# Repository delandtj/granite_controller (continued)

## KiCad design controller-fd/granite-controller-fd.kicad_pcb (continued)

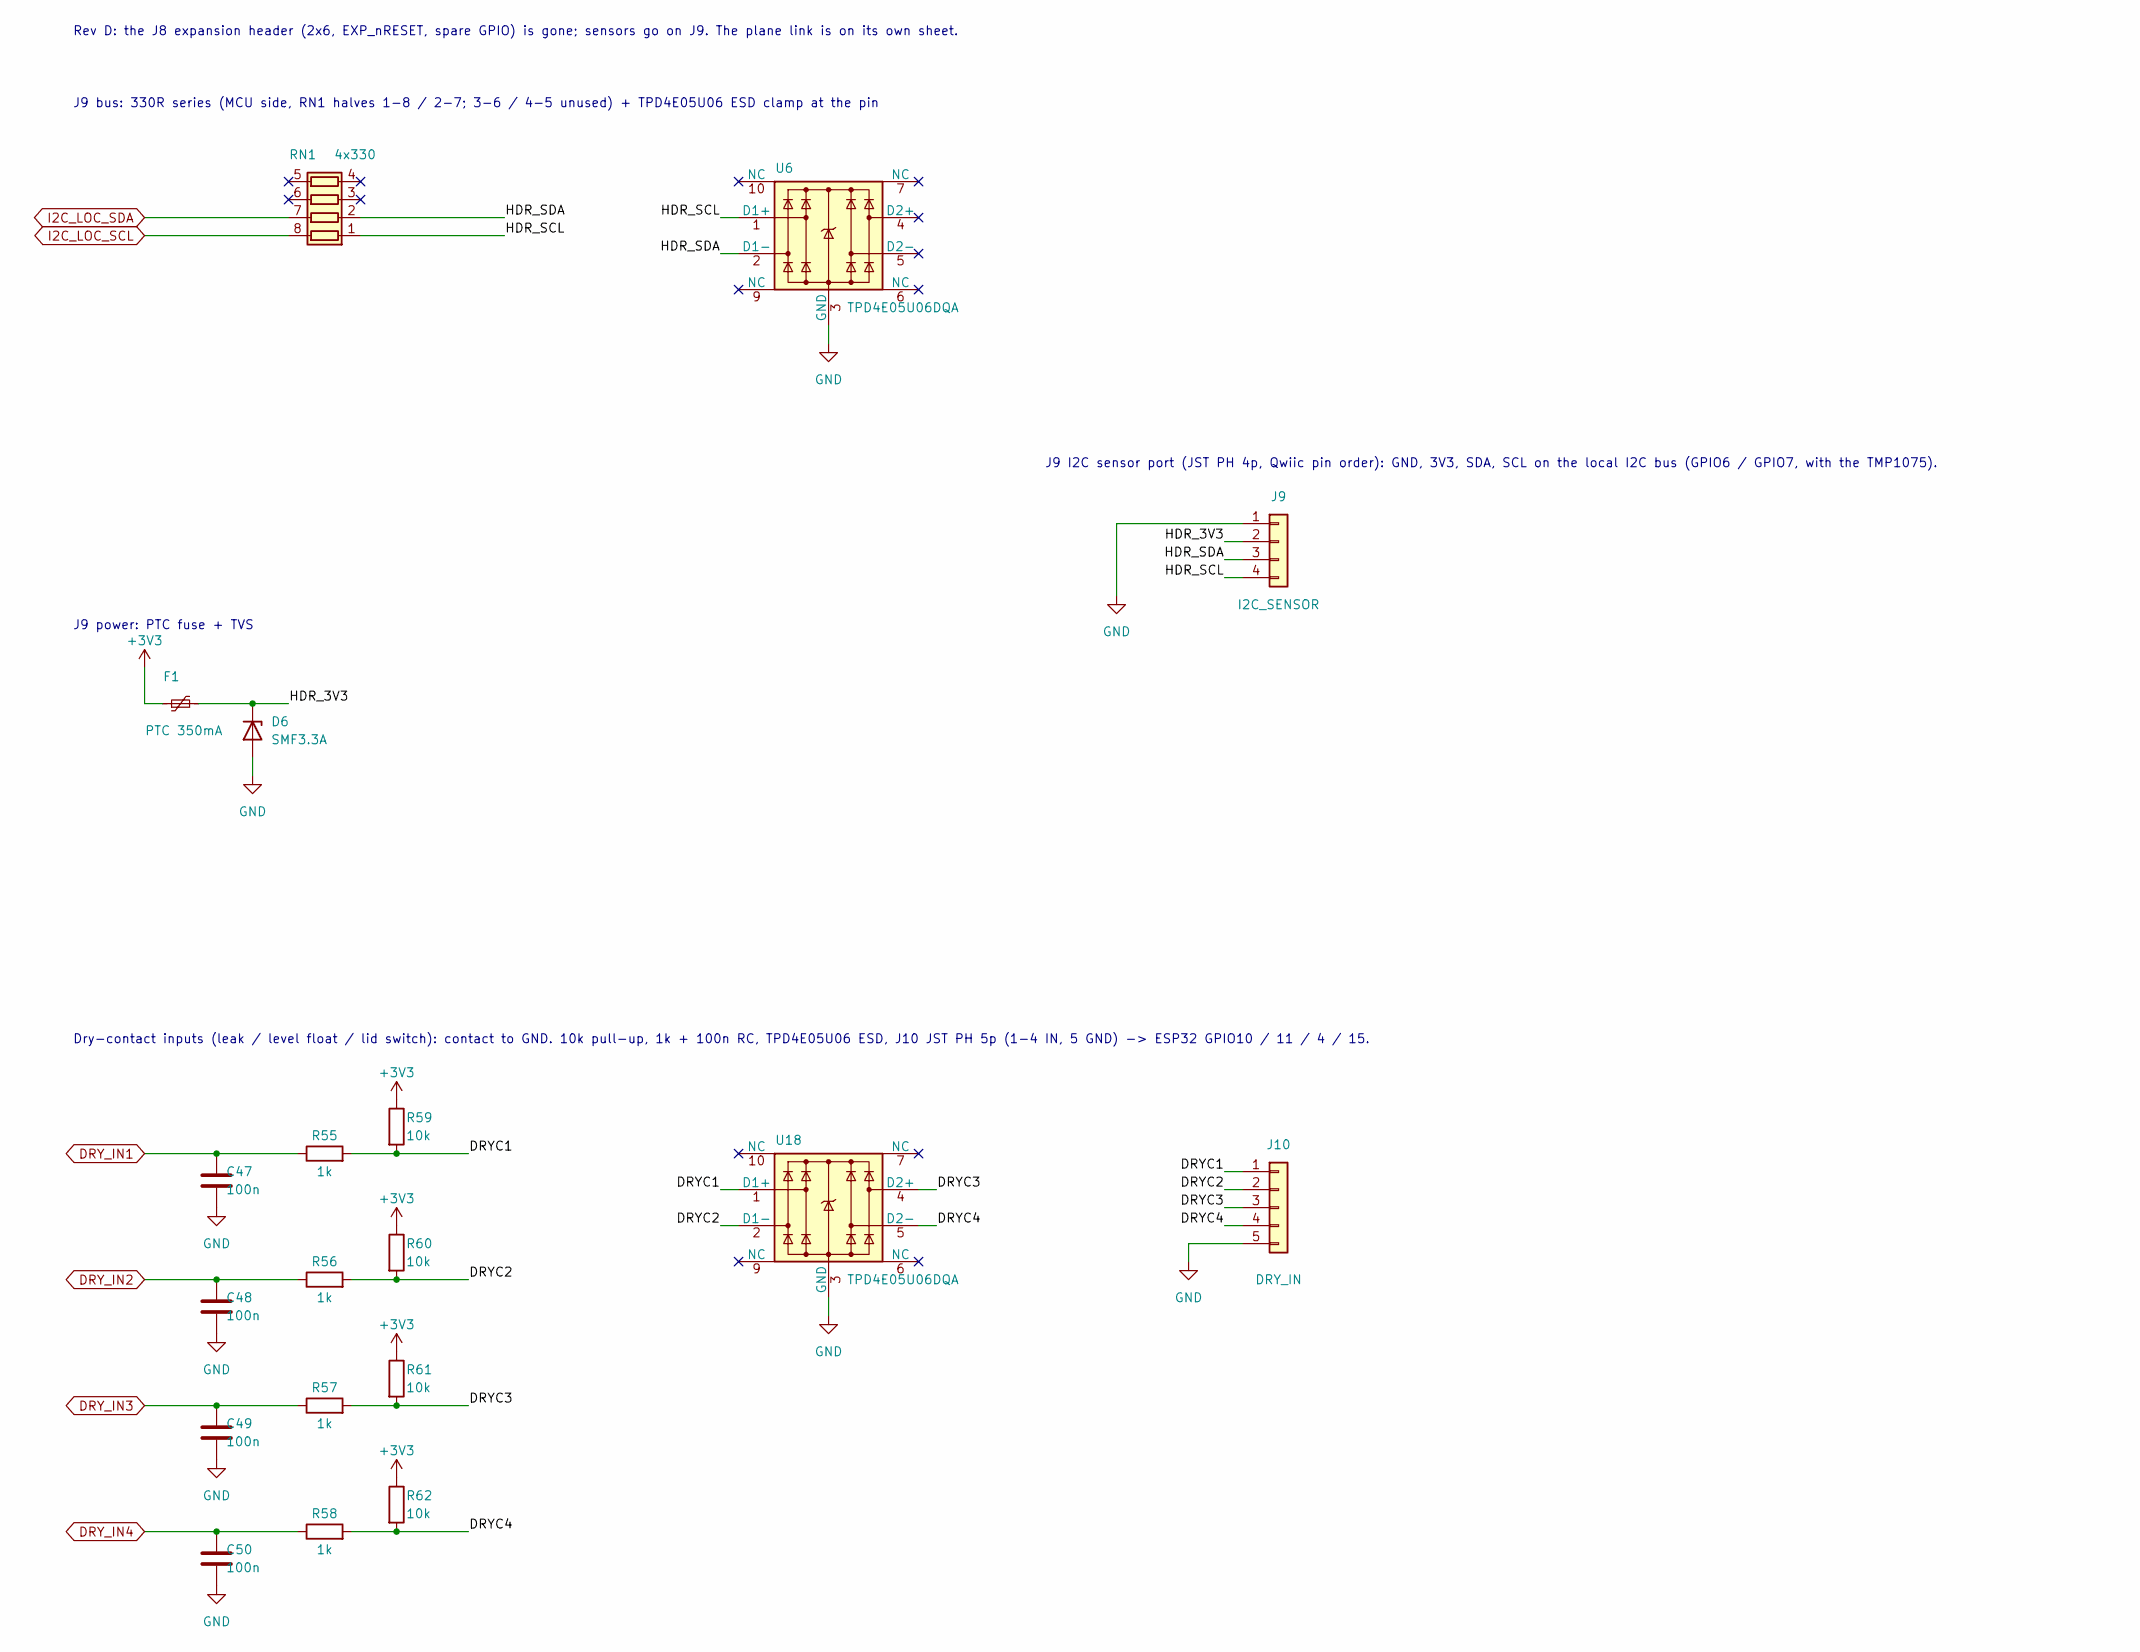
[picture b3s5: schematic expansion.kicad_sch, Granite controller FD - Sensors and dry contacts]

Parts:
C47, C48, C49, C50: 100n; C_0402_1005Metric; MPN CL05B104KO5NNNC; LCSC C1525
D6: SMF3.3A; D_SOD-123F; MPN SMF3.3A; LCSC C37331473
F1: PTC 350mA; Fuse_0805_2012Metric; MPN 0805L035/24XR; LCSC C7472565
J9: I2C_SENSOR; JST_PH_B4B-PH-K_1x04_P2.00mm_Vertical; MPN B4B-PH-K-S(LF)(SN); LCSC C131334
J10: DRY_IN; JST_PH_B5B-PH-K_1x05_P2.00mm_Vertical; MPN B5B-PH-K-S(LF)(SN); LCSC C157993
R55, R56, R57, R58: 1k; R_0402_1005Metric; MPN 0402WGF1001TCE; LCSC C11702
R59, R60, R61, R62: 10k; R_0402_1005Metric; MPN 0402WGF1002TCE; LCSC C25744
RN1: 4x330; R_Array_Convex_4x0402; MPN 4D02WGJ0331TCE; LCSC C43557
U6, U18: TPD4E05U06DQA; USON-10_2.5x1.0mm_P0.5mm; MPN TPD4E05U06DQAR; LCSC C138714

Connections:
+3V3: F1.1, R59.1, R60.1, R61.1, R62.1; also elsewhere on the board
/Sensors and dry contacts/DRYC1: J10.1, R55.2, R59.2, U18.1 (D1+)
/Sensors and dry contacts/DRYC2: J10.2, R56.2, R60.2, U18.2 (D1-)
/Sensors and dry contacts/DRYC3: J10.3, R57.2, R61.2, U18.4 (D2+)
/Sensors and dry contacts/DRYC4: J10.4, R58.2, R62.2, U18.5 (D2-)
/Sensors and dry contacts/HDR_3V3: D6.1 (K), F1.2, J9.2
/Sensors and dry contacts/HDR_SCL: J9.4, RN1.1 (R1.1), U6.1 (D1+)
/Sensors and dry contacts/HDR_SDA: J9.3, RN1.2 (R2.1), U6.2 (D1-)
DRY_IN1: C47.1, R55.1; also elsewhere on the board
DRY_IN2: C48.1, R56.1; also elsewhere on the board
DRY_IN3: C49.1, R57.1; also elsewhere on the board
DRY_IN4: C50.1, R58.1; also elsewhere on the board
GND: C47.2, C48.2, C49.2, C50.2, D6.2 (A), J9.1, J10.5, U6.3 (GND), U6.8 (GND), U18.3 (GND), U18.8 (GND); also elsewhere on the board
I2C_LOC_SCL: RN1.8 (R1.2); also elsewhere on the board
I2C_LOC_SDA: RN1.7 (R2.2); also elsewhere on the board

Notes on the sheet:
Rev D: the J8 expansion header (2x6, EXP_nRESET, spare GPIO) is gone; sensors go on J9. The plane link is on its own sheet.
J9 bus: 330R series (MCU side, RN1 halves 1-8 / 2-7; 3-6 / 4-5 unused) + TPD4E05U06 ESD clamp at the pin
J9 power: PTC fuse + TVS
J9 I2C sensor port (JST PH 4p, Qwiic pin order): GND, 3V3, SDA, SCL on the local I2C bus (GPIO6 / GPIO7, with the TMP1075).
Dry-contact inputs (leak / level float / lid switch): contact to GND. 10k pull-up, 1k + 100n RC, TPD4E05U06 ESD, J10 JST PH 5p (1-4 IN, 5 GND) -> ESP32 GPIO10 / 11 / 4 / 15.

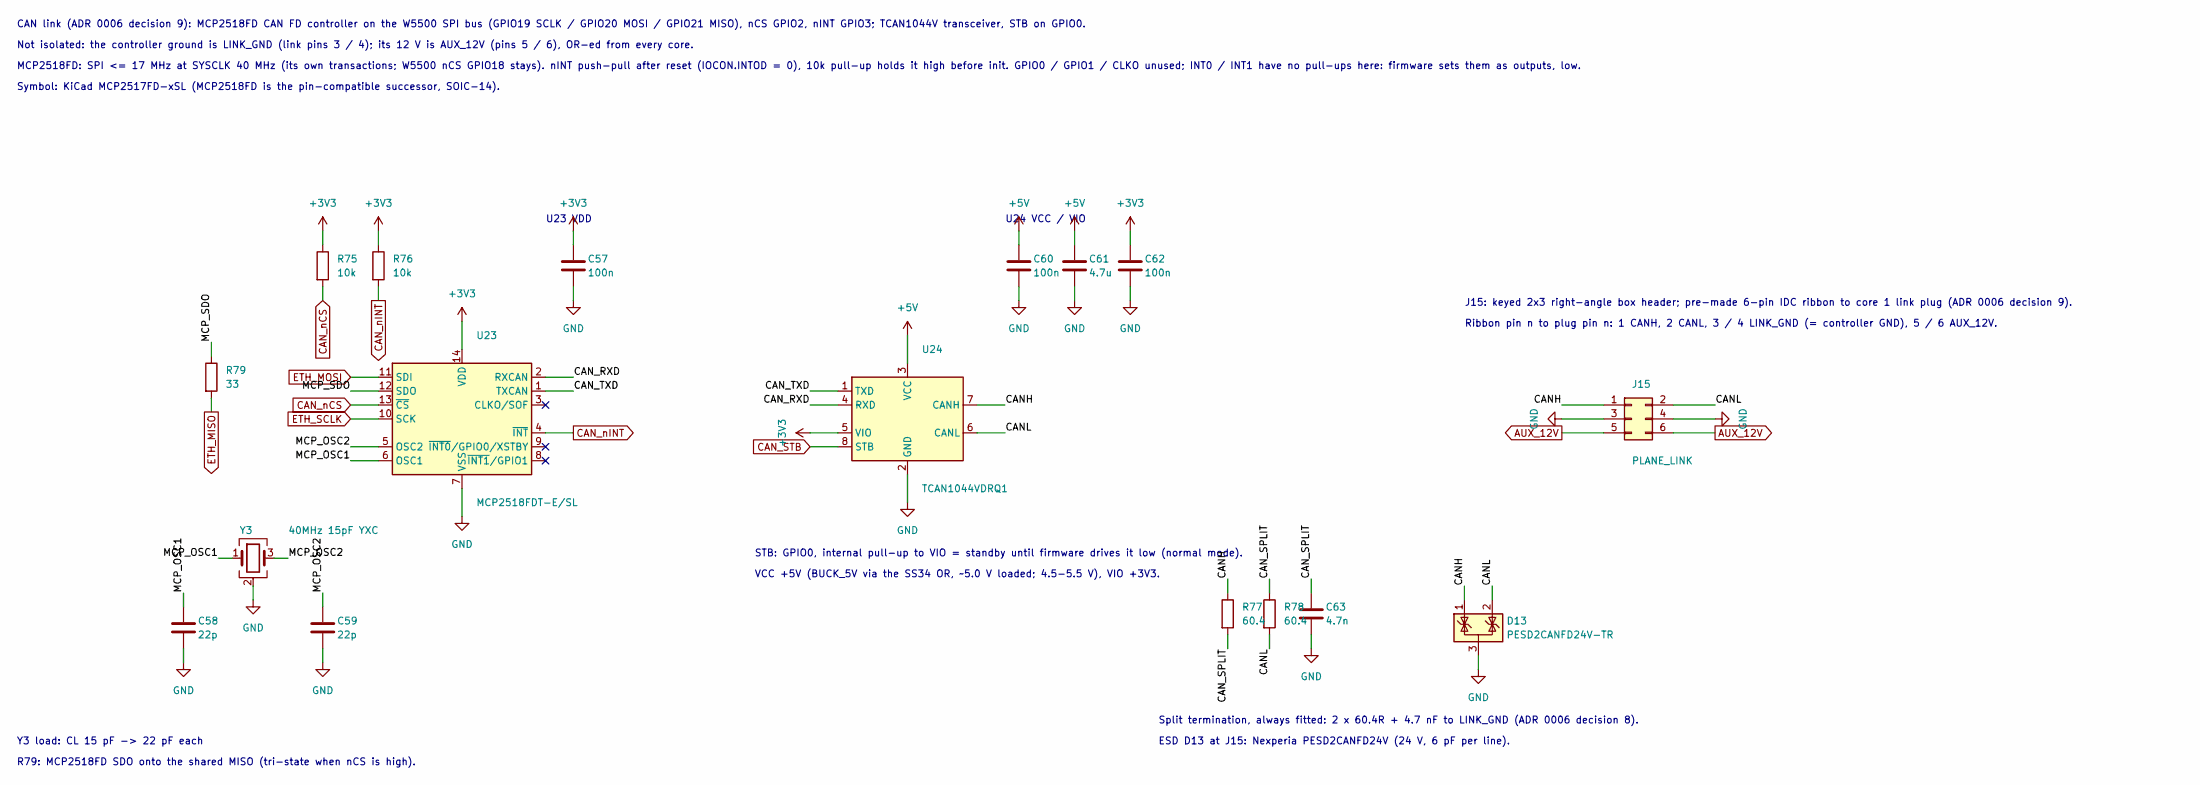
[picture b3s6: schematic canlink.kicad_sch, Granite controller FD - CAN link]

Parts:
C57, C60, C62: 100n; C_0402_1005Metric; MPN CL05B104KO5NNNC; LCSC C1525
C58, C59: 22p; C_0402_1005Metric; MPN 0402CG220J500NT; LCSC C1555
C61: 4.7u; C_0603_1608Metric; MPN CL10A475KO8NNNC; LCSC C19666
C63: 4.7n; C_0402_1005Metric; MPN 0402B472K500NT; LCSC C1538
D13: PESD2CANFD24V-TR; SOT-23; MPN PESD2CANFD24V-TR; LCSC C552486
J15: PLANE_LINK; IDC-Header_2x03_P2.54mm_Horizontal; MPN 2.54-2*3P Bent Header; LCSC C34945
R75, R76: 10k; R_0402_1005Metric; MPN 0402WGF1002TCE; LCSC C25744
R77, R78: 60.4; R_0402_1005Metric; MPN 0402WGF604JTCE; LCSC C60310
R79: 33; R_0402_1005Metric; MPN 0402WGF330JTCE; LCSC C25105
U23: MCP2518FDT-E/SL; SOIC-14_3.9x8.7mm_P1.27mm; MPN MCP2518FDT-E/SL; LCSC C626758
U24: TCAN1044VDRQ1; SOIC-8_3.9x4.9mm_P1.27mm; MPN TCAN1044VDRQ1; LCSC C1852061
Y3: 40MHz 15pF YXC; Crystal_SMD_Abracon_ABM8G-4Pin_3.2x2.5mm; MPN X322540MPB4SI; LCSC C9010

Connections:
+3V3: C57.1, C62.1, R75.1, R76.1, U23.14 (VDD), U24.5 (VIO); also elsewhere on the board
+5V: C60.1, C61.1, U24.3 (VCC); also elsewhere on the board
/CAN link/CANH: D13.1 (K), J15.1, R77.1, U24.7 (CANH)
/CAN link/CANL: D13.2 (K), J15.2, R78.2, U24.6 (CANL)
/CAN link/CAN_RXD: U23.2 (RXCAN), U24.4 (RXD)
/CAN link/CAN_SPLIT: C63.1, R77.2, R78.1
/CAN link/CAN_TXD: U23.1 (TXCAN), U24.1 (TXD)
/CAN link/MCP_OSC1: C58.1, U23.6 (OSC1), Y3.1
/CAN link/MCP_OSC2: C59.1, U23.5 (OSC2), Y3.3
/CAN link/MCP_SDO: R79.1, U23.12 (SDO)
AUX_12V: J15.5, J15.6; also elsewhere on the board
CAN_STB: U24.8 (STB); also elsewhere on the board
CAN_nCS: R75.2, U23.13 (~CS); also elsewhere on the board
CAN_nINT: R76.2, U23.4 (~INT); also elsewhere on the board
ETH_MISO: R79.2; also elsewhere on the board
ETH_MOSI: U23.11 (SDI); also elsewhere on the board
ETH_SCLK: U23.10 (SCK); also elsewhere on the board
GND: C57.2, C58.2, C59.2, C60.2, C61.2, C62.2, C63.2, D13.3 (A), J15.3, J15.4, U23.7 (VSS), U24.2 (GND), Y3.2 (G), Y3.4 (G); also elsewhere on the board

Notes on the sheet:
CAN link (ADR 0006 decision 9): MCP2518FD CAN FD controller on the W5500 SPI bus (GPIO19 SCLK / GPIO20 MOSI / GPIO21 MISO), nCS GPIO2, nINT GPIO3; TCAN1044V transceiver, STB on GPIO0.
Not isolated: the controller ground is LINK_GND (link pins 3 / 4); its 12 V is AUX_12V (pins 5 / 6), OR-ed from every core.
MCP2518FD: SPI <= 17 MHz at SYSCLK 40 MHz (its own transactions; W5500 nCS GPIO18 stays). nINT push-pull after reset (IOCON.INTOD = 0), 10k pull-up holds it high before init. GPIO0 / GPIO1 / CLKO unused; INT0 / INT1 have no pull-ups here: firmware sets them as outputs, low.
Symbol: KiCad MCP2517FD-xSL (MCP2518FD is the pin-compatible successor, SOIC-14).
R79: MCP2518FD SDO onto the shared MISO (tri-state when nCS is high).
U23 VDD
Y3 load: CL 15 pF -> 22 pF each
STB: GPIO0, internal pull-up to VIO = standby until firmware drives it low (normal mode).
VCC +5V (BUCK_5V via the SS34 OR, ~5.0 V loaded; 4.5-5.5 V), VIO +3V3.
U24 VCC / VIO
J15: keyed 2x3 right-angle box header; pre-made 6-pin IDC ribbon to core 1 link plug (ADR 0006 decision 9).
Ribbon pin n to plug pin n: 1 CANH, 2 CANL, 3 / 4 LINK_GND (= controller GND), 5 / 6 AUX_12V.
Split termination, always fitted: 2 x 60.4R + 4.7 nF to LINK_GND (ADR 0006 decision 8).
ESD D13 at J15: Nexperia PESD2CANFD24V (24 V, 6 pF per line).

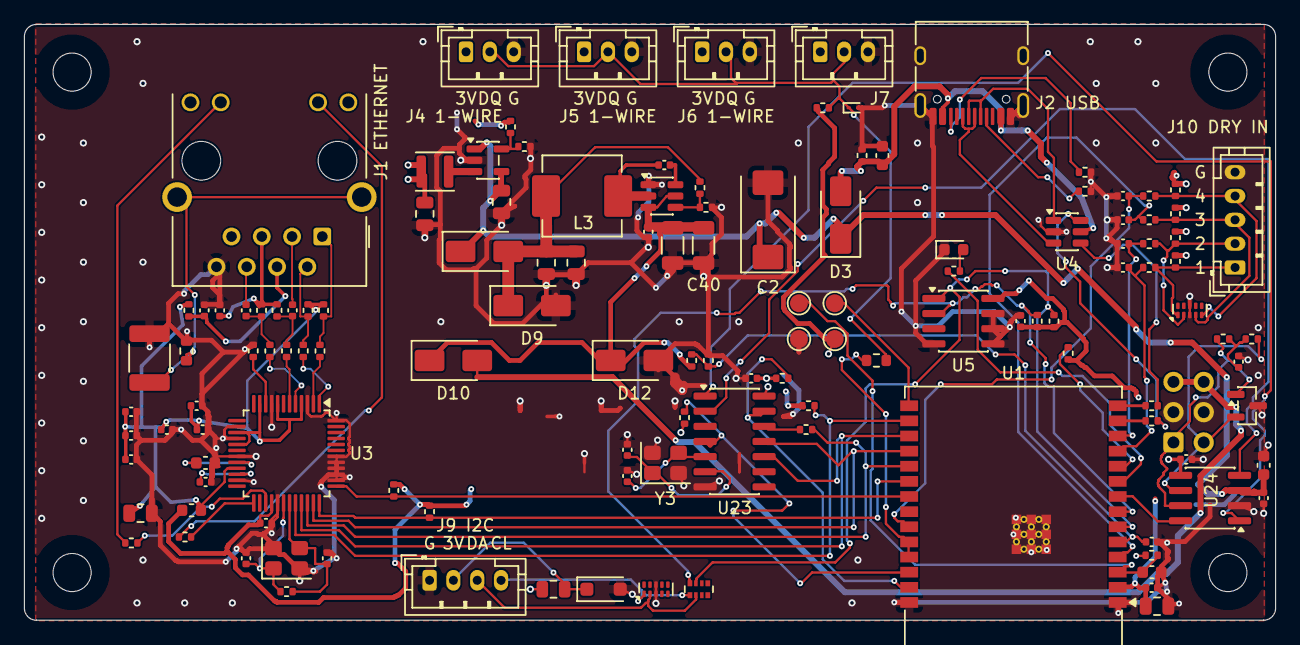
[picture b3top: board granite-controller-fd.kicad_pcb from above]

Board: 4 copper layers, 105.0 x 50.0 mm, 134 parts (1 on the bottom side), 81 nets.

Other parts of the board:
H1, H2, H3, H4: MountingHole_3.2mm_M3

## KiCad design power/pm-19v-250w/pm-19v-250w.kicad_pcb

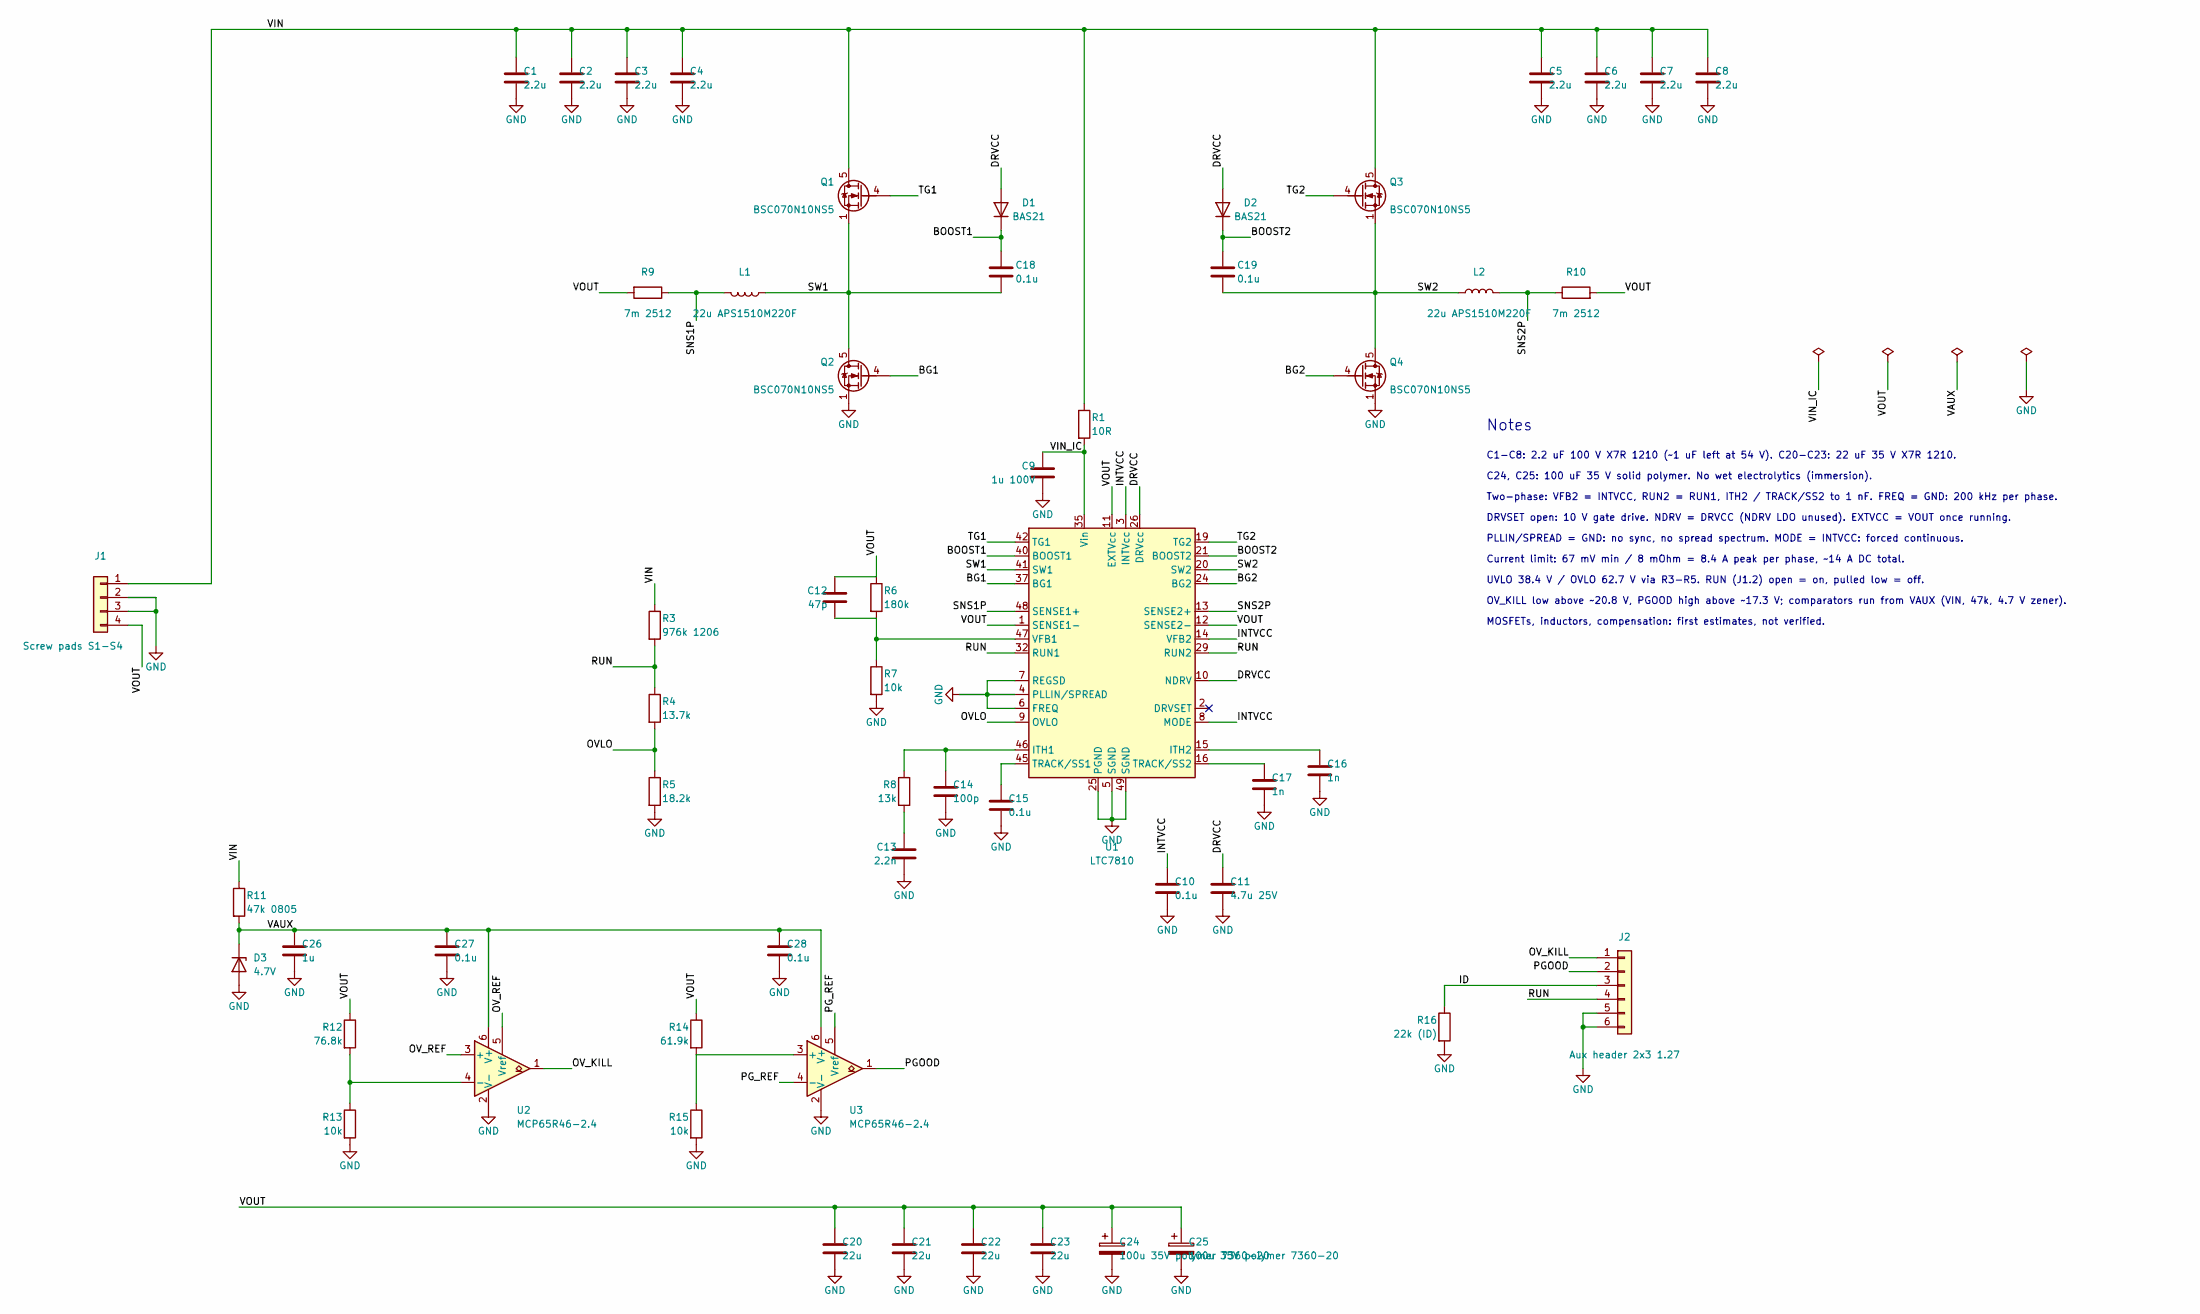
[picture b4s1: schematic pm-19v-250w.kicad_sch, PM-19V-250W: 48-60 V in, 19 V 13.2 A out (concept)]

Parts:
C1, C2, C3, C4, C5, C6, C7, C8: 2.2u; C_1210_3225Metric; LCSC C5449052
C9: 1u 100V; C_0805_2012Metric; LCSC C5370002
C10, C15, C18, C19, C27, C28: 0.1u; C_0402_1005Metric; LCSC C307331
C11: 4.7u 25V; C_0805_2012Metric; LCSC C354262
C12: 47p; C_0402_1005Metric; LCSC C1567
C13: 2.2n; C_0402_1005Metric; LCSC C2980802
C14: 100p; C_0402_1005Metric; LCSC C1546
C16, C17: 1n; C_0402_1005Metric; LCSC C1523
C20, C21, C22, C23: 22u; C_1210_3225Metric; LCSC C778721
C24, C25: 100u 35V polymer 7360-20; CP_EIA-7360-38_Kemet-E; LCSC C2158991
C26: 1u; C_0402_1005Metric; LCSC C52923
D1, D2: BAS21; D_SOD-323; LCSC C82466
D3: 4.7V; D_SOD-323; LCSC C107713
J1: Screw pads S1-S4; PM_Mount_M2
J2: Aux header 2x3 1.27; PM_Aux_Header_2x03_P1.27; LCSC C41376035
L1, L2: 22u APS1510M220F; L_Coilcraft_XAL1510-223; LCSC C49261404
Q1, Q2, Q3, Q4: BSC070N10NS5; TDSON-8-1; LCSC C534364
R1: 10R; R_0603_1608Metric; LCSC C22859
R3: 976k 1206; R_1206_3216Metric; LCSC C247164
R4: 13.7k; R_0603_1608Metric; LCSC C22793
R5: 18.2k; R_0402_1005Metric; LCSC C25859
R6: 180k; R_0402_1005Metric; LCSC C25760
R7, R13, R15: 10k; R_0402_1005Metric; LCSC C25744
R8: 13k; R_0402_1005Metric; LCSC C25754
R9, R10: 7m 2512; R_2512_6332Metric; LCSC C20608751
R11: 47k 0805; R_0805_2012Metric; LCSC C17713
R12: 76.8k; R_0402_1005Metric; LCSC C26987
R14: 61.9k; R_0402_1005Metric; LCSC C2933106
R16: 22k (ID); R_0603_1608Metric; LCSC C31850
U1: LTC7810; LQFP-48-1EP_7x7mm_P0.5mm_EP3.6x3.6mm; LCSC C581067
U2, U3: MCP65R46-2.4; SOT-23-6; LCSC C623510

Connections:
/BG1: Q2.4 (G), U1.37 (BG1)
/BG2: Q4.4 (G), U1.24 (BG2)
/BOOST1: C18.1, D1.1 (K), U1.40 (BOOST1)
/BOOST2: C19.1, D2.1 (K), U1.21 (BOOST2)
/DRVCC: C11.1, D1.2 (A), D2.2 (A), U1.10 (NDRV), U1.26 (DRVcc)
/ID: J2.3, R16.1
/INTVCC: C10.1, U1.3 (INTVcc), U1.8 (MODE), U1.14 (VFB2)
/OVLO: R4.2, R5.1, U1.9 (OVLO)
/OV_KILL: J2.1, U2.1
/OV_REF: U2.3 (+), U2.5 (Vref)
/PGOOD: J2.2, U3.1
/PG_REF: U3.4 (-), U3.5 (Vref)
/RUN: J2.4, R3.2, R4.1, U1.29 (RUN2), U1.32 (RUN1)
/SNS1P: L1.2, R9.1, U1.48 (SENSE1+)
/SNS2P: L2.2, R10.1, U1.13 (SENSE2+)
/SW1: C18.2, L1.1, Q1.1 (S), Q1.2 (S), Q1.3 (S), Q2.5 (D), U1.41 (SW1)
/SW2: C19.2, L2.1, Q3.1 (S), Q3.2 (S), Q3.3 (S), Q4.5 (D), U1.20 (SW2)
/TG1: Q1.4 (G), U1.42 (TG1)
/TG2: Q3.4 (G), U1.19 (TG2)
/VAUX: C26.1, C27.1, C28.1, D3.1 (K), R11.2, U2.6 (V+), U3.6 (V+)
/VIN: C1.1, C2.1, C3.1, C4.1, C5.1, C6.1, C7.1, C8.1, J1.1, Q1.5 (D), Q3.5 (D), R1.1, R3.1, R11.1
/VIN_IC: C9.1, R1.2, U1.35 (Vin)
/VOUT: C12.1, C20.1, C21.1, C22.1, C23.1, C24.1, C25.1, J1.4, R6.1, R9.2, R10.2, R12.1, R14.1, U1.1 (SENSE1-), U1.11 (EXTVcc), U1.12 (SENSE2-)
GND: C1.2, C2.2, C3.2, C4.2, C5.2, C6.2, C7.2, C8.2, C9.2, C10.2, C11.2, C13.2, C14.2, C15.2, C16.2, C17.2, C20.2, C21.2, C22.2, C23.2, C24.2, C25.2, C26.2, C27.2, C28.2, D3.2 (A), J1.2, J1.3, J2.5, J2.6, Q2.1 (S), Q2.2 (S), Q2.3 (S), Q4.1 (S), Q4.2 (S), Q4.3 (S), R5.2, R7.2, R13.2, R15.2, R16.2, U1.4 (PLLIN/SPREAD), U1.5 (SGND), U1.6 (FREQ), U1.7 (REGSD), U1.25 (PGND), U1.49 (SGND), U2.2 (V-), U3.2 (V-)
unnamed: C13.1, R8.2
unnamed: C14.1, R8.1, U1.46 (ITH1)
unnamed: C16.1, U1.15 (ITH2)
unnamed: C15.1, U1.45 (TRACK/SS1)
unnamed: C17.1, U1.16 (TRACK/SS2)
unnamed: C12.2, R6.2, R7.1, U1.47 (VFB1)
unnamed: R12.2, R13.1, U2.4 (-)
unnamed: R14.2, R15.1, U3.3 (+)

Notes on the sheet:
Notes
C1-C8: 2.2 uF 100 V X7R 1210 (~1 uF left at 54 V). C20-C23: 22 uF 35 V X7R 1210.
C24, C25: 100 uF 35 V solid polymer. No wet electrolytics (immersion).
Two-phase: VFB2 = INTVCC, RUN2 = RUN1, ITH2 / TRACK/SS2 to 1 nF. FREQ = GND: 200 kHz per phase.
DRVSET open: 10 V gate drive. NDRV = DRVCC (NDRV LDO unused). EXTVCC = VOUT once running.
PLLIN/SPREAD = GND: no sync, no spread spectrum. MODE = INTVCC: forced continuous.
Current limit: 67 mV min / 8 mOhm = 8.4 A peak per phase, ~14 A DC total.
UVLO 38.4 V / OVLO 62.7 V via R3-R5. RUN (J1.2) open = on, pulled low = off.
OV_KILL low above ~20.8 V, PGOOD high above ~17.3 V; comparators run from VAUX (VIN, 47k, 4.7 V zener).
MOSFETs, inductors, compensation: first estimates, not verified.

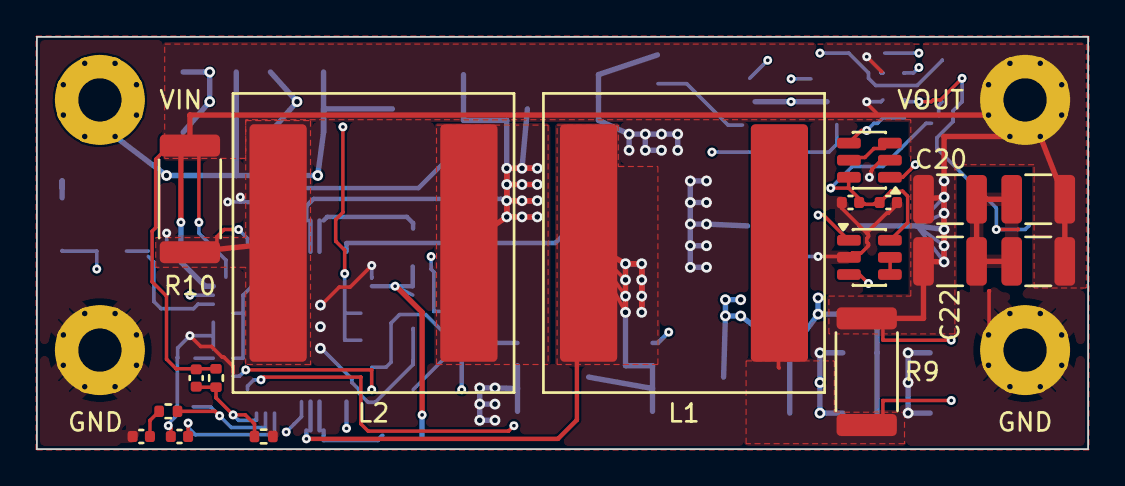
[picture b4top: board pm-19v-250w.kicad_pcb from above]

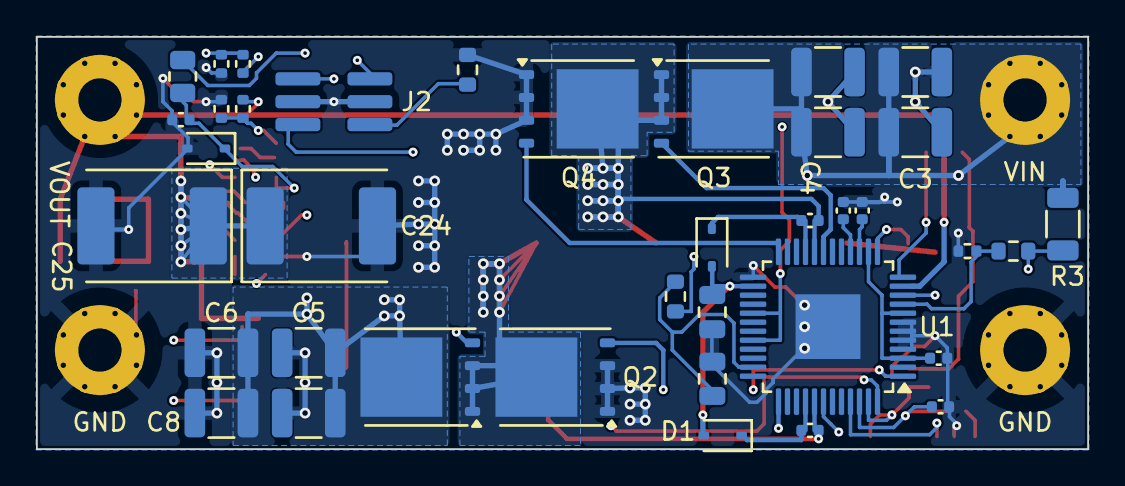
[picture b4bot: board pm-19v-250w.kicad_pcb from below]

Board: 4 copper layers, 58.4 x 22.9 mm, 57 parts (38 on the bottom side), 32 nets.

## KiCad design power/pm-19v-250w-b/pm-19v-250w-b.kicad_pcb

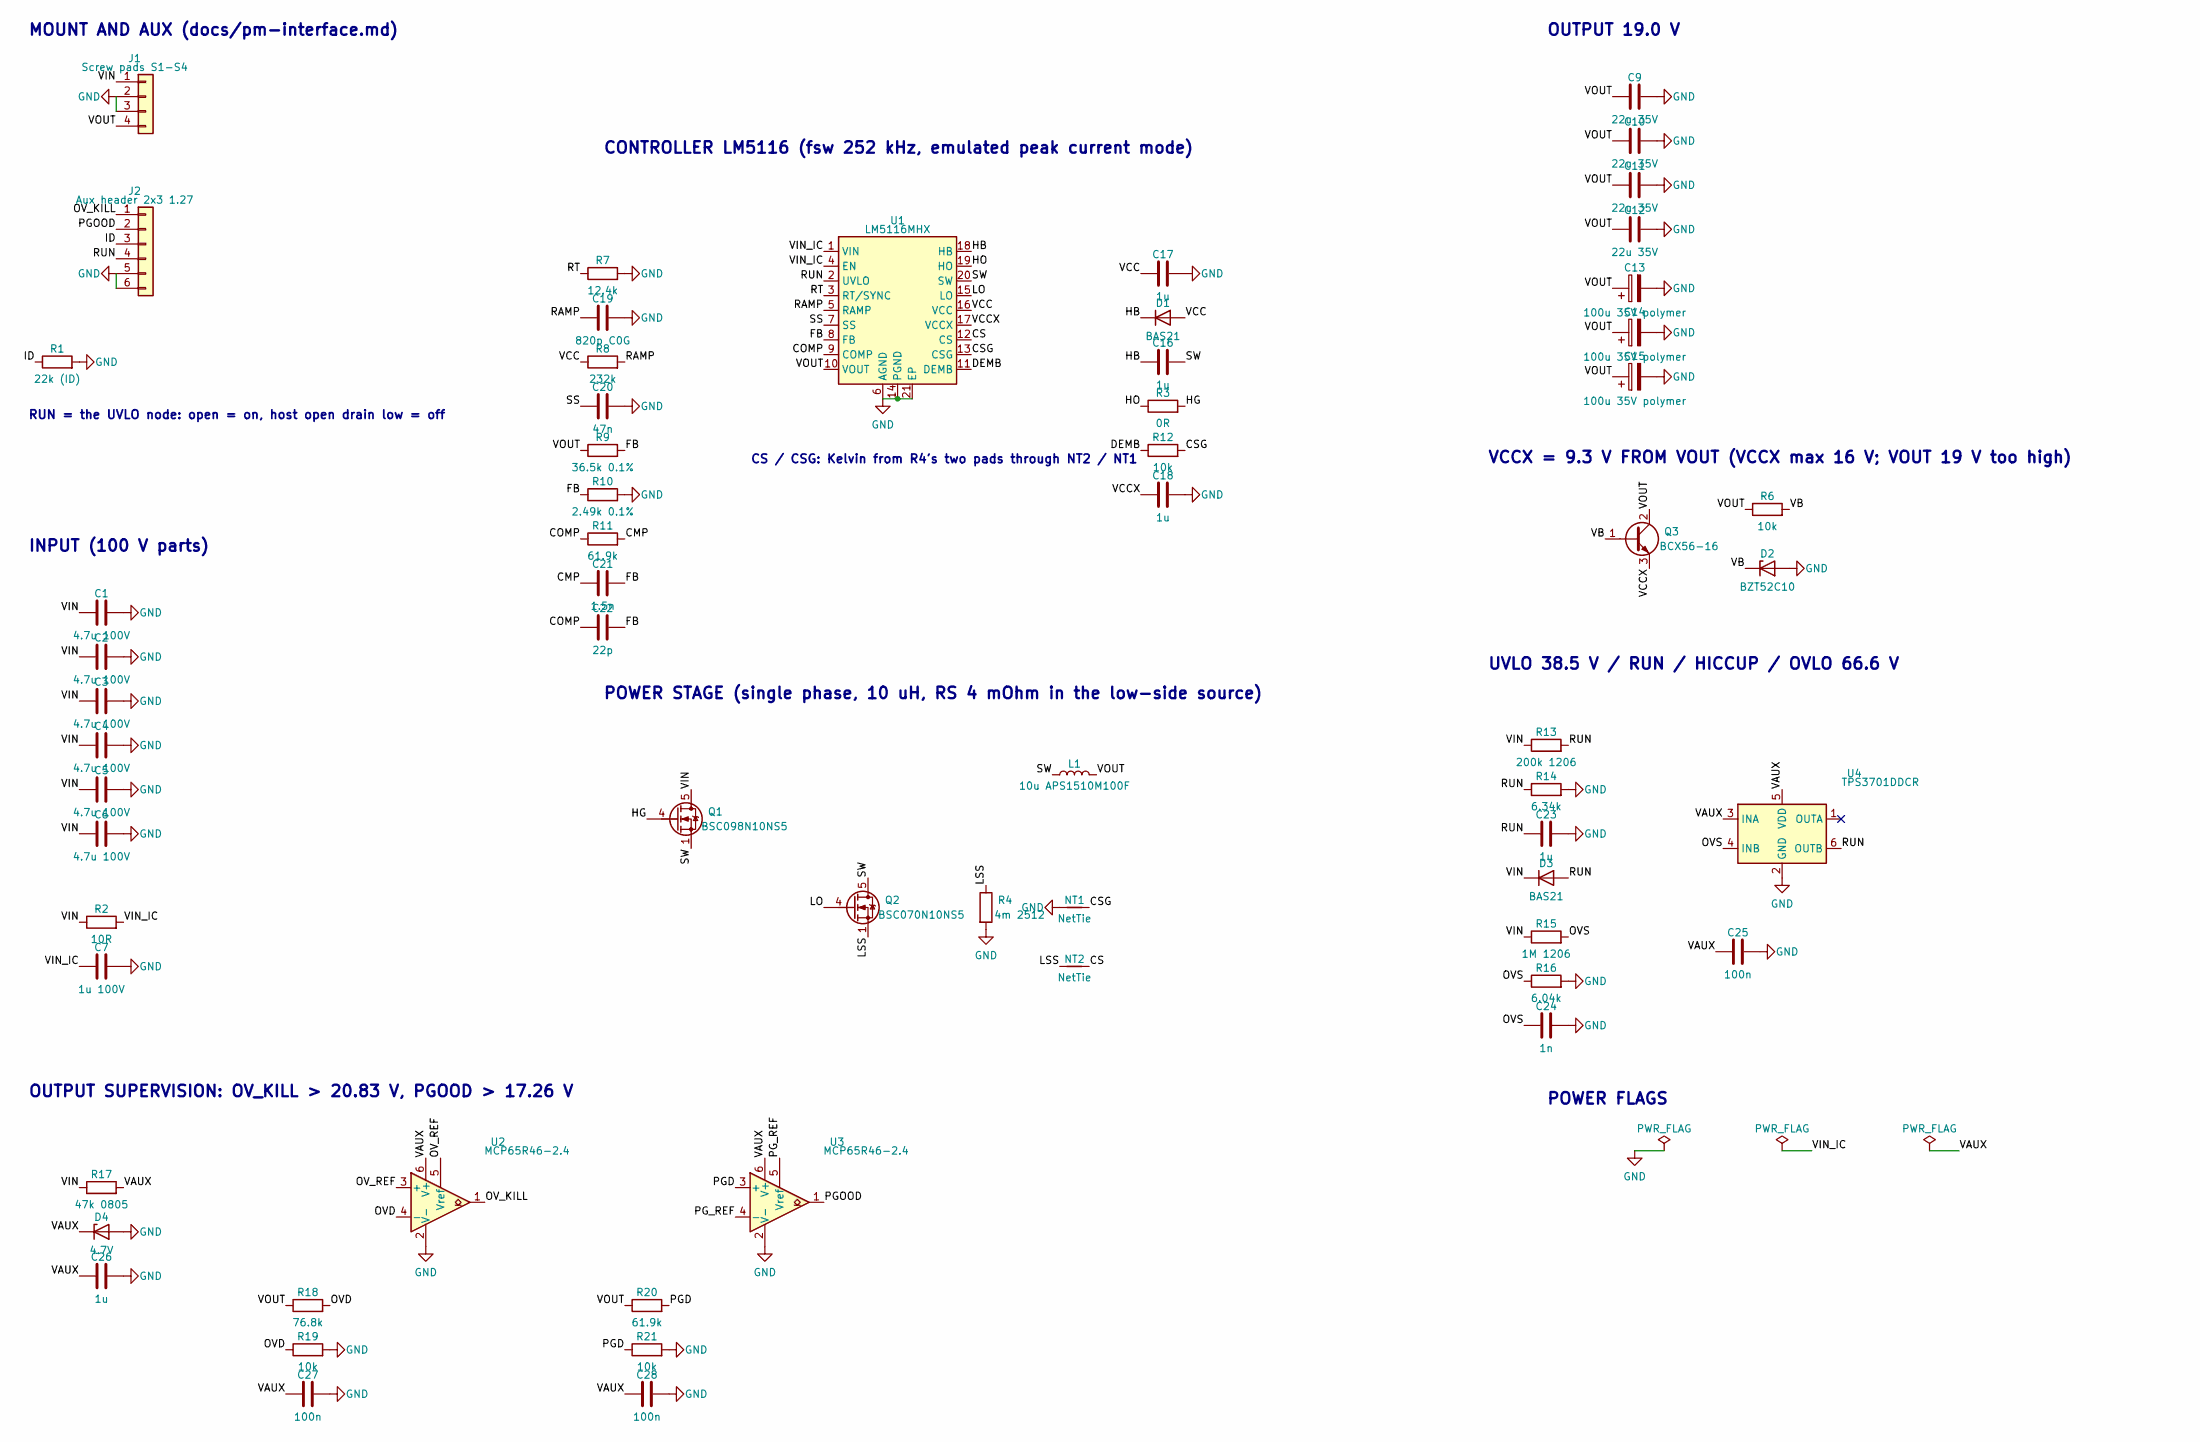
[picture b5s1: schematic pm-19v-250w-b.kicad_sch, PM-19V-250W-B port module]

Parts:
C1, C2, C3, C4, C5, C6: 4.7u 100V; C_1210_3225Metric; LCSC C381466
C7: 1u 100V; C_0805_2012Metric; LCSC C5370002
C9, C10, C11, C12: 22u 35V; C_1210_3225Metric; LCSC C778721
C13, C14, C15: 100u 35V polymer; CP_Elec_6.3x7.7; LCSC C46550467
C16, C17, C18, C23, C26: 1u; C_0402_1005Metric; LCSC C52923
C19: 820p C0G; C_0402_1005Metric; LCSC C161159
C20: 47n; C_0402_1005Metric; LCSC C272875
C21: 1.5n; C_0402_1005Metric; LCSC C107022
C22: 22p; C_0402_1005Metric; LCSC C1555
C24: 1n; C_0402_1005Metric; LCSC C1523
C25, C27, C28: 100n; C_0402_1005Metric; LCSC C307331
D1, D3: BAS21; D_SOD-323; LCSC C82466
D2: BZT52C10; D_SOD-123; LCSC C2103
D4: 4.7V; D_SOD-323; LCSC C107713
J1: Screw pads S1-S4; PM_Mount_M2
J2: Aux header 2x3 1.27; PM_Aux_Header_2x03_P1.27; LCSC C41376035
L1: 10u APS1510M100F; L_Coilcraft_XAL1510-103; LCSC C49261402
NT1, NT2: NetTie; NetTie-2_SMD_Pad0.5mm
Q1: BSC098N10NS5; TDSON-8-1; LCSC C534398
Q2: BSC070N10NS5; TDSON-8-1; LCSC C534364
Q3: BCX56-16; SOT-89-3; LCSC C123402
R1: 22k (ID); R_0603_1608Metric; LCSC C31850
R2: 10R; R_0603_1608Metric; LCSC C22859
R3: 0R; R_0402_1005Metric; LCSC C17168
R4: 4m 2512; R_2512_6332Metric; LCSC C459681
R6, R12, R19, R21: 10k; R_0402_1005Metric; LCSC C25744
R7: 12.4k; R_0402_1005Metric; LCSC C2929935
R8: 232k; R_0402_1005Metric; LCSC C3013159
R9: 36.5k 0.1%; R_0402_1005Metric; LCSC C852741
R10: 2.49k 0.1%; R_0402_1005Metric; LCSC C852700
R11, R20: 61.9k; R_0402_1005Metric; LCSC C2933106
R13: 200k 1206; R_1206_3216Metric; LCSC C17954
R14: 6.34k; R_0402_1005Metric; LCSC C5713274
R15: 1M 1206; R_1206_3216Metric; LCSC C17927
R16: 6.04k; R_0402_1005Metric; LCSC C2998182
R17: 47k 0805; R_0805_2012Metric; LCSC C17713
R18: 76.8k; R_0402_1005Metric; LCSC C26987
U1: LM5116MHX; HTSSOP-20-1EP_4.4x6.5mm_P0.65mm_EP3.4x6.5mm_ThermalVias; LCSC C13755
U2, U3: MCP65R46-2.4; SOT-23-6; LCSC C623510
U4: TPS3701DDCR; SOT-23-6; LCSC C132788

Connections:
/CMP: C21.1, R11.2
/COMP: C22.1, R11.1, U1.9 (COMP)
/CS: NT2.2, U1.12 (CS)
/CSG: NT1.2, R12.2, U1.13 (CSG)
/DEMB: R12.1, U1.11 (DEMB)
/FB: C21.2, C22.2, R9.2, R10.1, U1.8 (FB)
/HB: C16.1, D1.1 (K), U1.18 (HB)
/HG: Q1.4 (G), R3.2
/HO: R3.1, U1.19 (HO)
/ID: J2.3, R1.1
/LO: Q2.4 (G), U1.15 (LO)
/LSS: NT2.1, Q2.1 (S), Q2.2 (S), Q2.3 (S), R4.1
/OVD: R18.2, R19.1, U2.4 (-)
/OVS: C24.1, R15.2, R16.1, U4.4 (INB)
/OV_KILL: J2.1, U2.1
/OV_REF: U2.3 (+), U2.5 (Vref)
/PGD: R20.2, R21.1, U3.3 (+)
/PGOOD: J2.2, U3.1
/PG_REF: U3.4 (-), U3.5 (Vref)
/RAMP: C19.1, R8.2, U1.5 (RAMP)
/RT: R7.1, U1.3 (RT/SYNC)
/RUN: C23.1, D3.2 (A), J2.4, R13.2, R14.1, U1.2 (UVLO), U4.6 (OUTB)
/SS: C20.1, U1.7 (SS)
/SW: C16.2, L1.1, Q1.1 (S), Q1.2 (S), Q1.3 (S), Q2.5 (D), U1.20 (SW)
/VAUX: C25.1, C26.1, C27.1, C28.1, D4.1 (K), R17.2, U2.6 (V+), U3.6 (V+), U4.3 (INA), U4.5 (VDD)
/VB: D2.1 (K), Q3.1 (B), R6.2
/VCC: C17.1, D1.2 (A), R8.1, U1.16 (VCC)
/VCCX: C18.1, Q3.3 (E), U1.17 (VCCX)
/VIN: C1.1, C2.1, C3.1, C4.1, C5.1, C6.1, D3.1 (K), J1.1, Q1.5 (D), R2.1, R13.1, R15.1, R17.1
/VIN_IC: C7.1, R2.2, U1.1 (VIN), U1.4 (EN)
/VOUT: C9.1, C10.1, C11.1, C12.1, C13.1, C14.1, C15.1, J1.4, L1.2, Q3.2 (C), R6.1, R9.1, R18.1, R20.1, U1.10 (VOUT)
GND: C1.2, C2.2, C3.2, C4.2, C5.2, C6.2, C7.2, C9.2, C10.2, C11.2, C12.2, C13.2, C14.2, C15.2, C17.2, C18.2, C19.2, C20.2, C23.2, C24.2, C25.2, C26.2, C27.2, C28.2, D2.2 (A), D4.2 (A), J1.2, J1.3, J2.5, J2.6, NT1.1, R1.2, R4.2, R7.2, R10.2, R14.2, R16.2, R19.2, R21.2, U1.6 (AGND), U1.14 (PGND), U1.21 (EP), U2.2 (V-), U3.2 (V-), U4.2 (GND)

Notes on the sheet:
MOUNT AND AUX (docs/pm-interface.md)
RUN = the UVLO node: open = on, host open drain low = off
INPUT (100 V parts)
CONTROLLER LM5116 (fsw 252 kHz, emulated peak current mode)
CS / CSG: Kelvin from R4's two pads through NT2 / NT1
POWER STAGE (single phase, 10 uH, RS 4 mOhm in the low-side source)
OUTPUT 19.0 V
VCCX = 9.3 V FROM VOUT (VCCX max 16 V; VOUT 19 V too high)
UVLO 38.5 V / RUN / HICCUP / OVLO 66.6 V
OUTPUT SUPERVISION: OV_KILL > 20.83 V, PGOOD > 17.26 V
POWER FLAGS

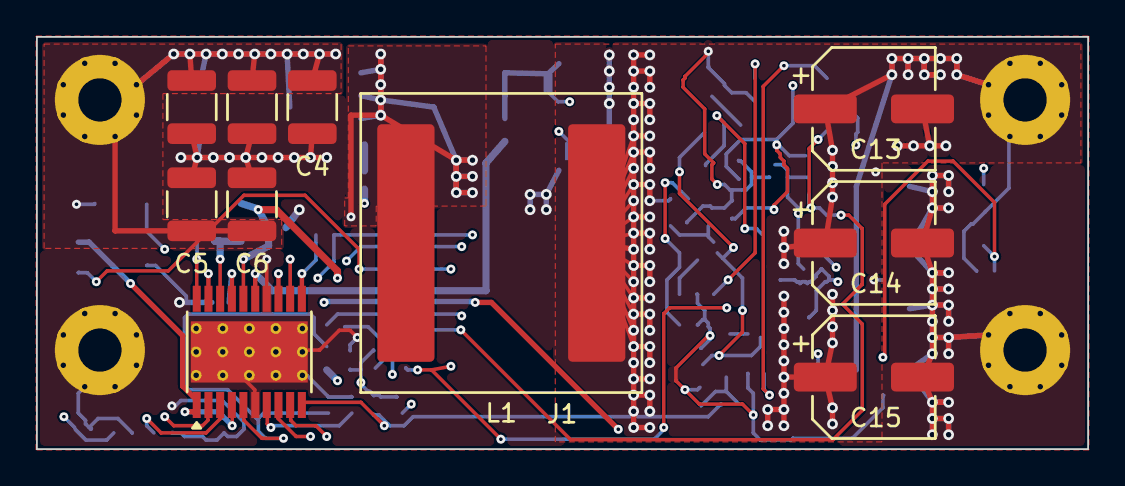
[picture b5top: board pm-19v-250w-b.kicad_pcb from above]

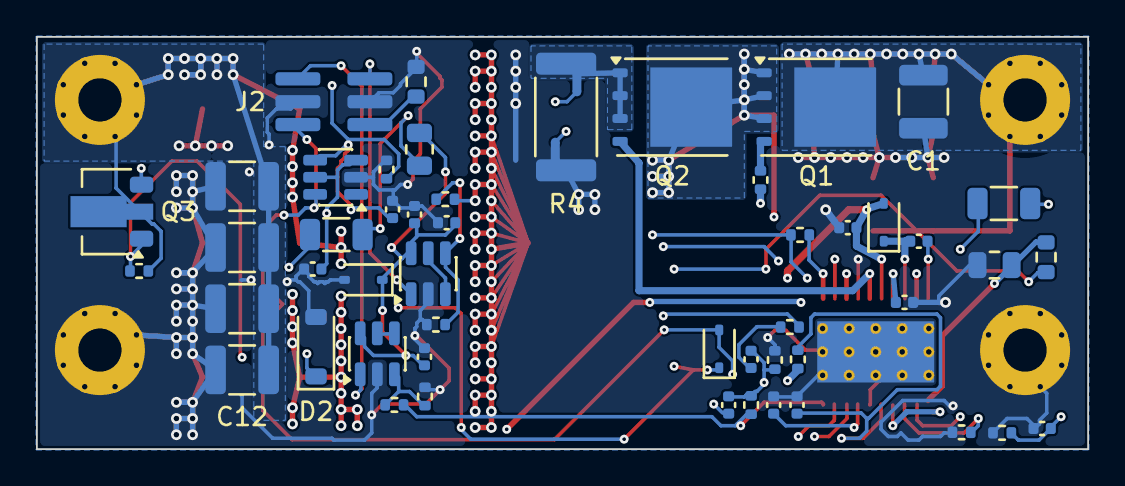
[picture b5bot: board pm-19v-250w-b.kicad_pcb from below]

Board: 4 copper layers, 58.4 x 22.9 mm, 63 parts (52 on the bottom side), 32 nets.
